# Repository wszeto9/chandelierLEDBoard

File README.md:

# Chandelier LED Board

A bright, addressible LED Panel that is used to light up a chandelier prop. Designed for MIT East Campus REX, Fall 2023.

[Interactive BOM](https://htmlpreview.github.io/?https://raw.githubusercontent.com/wszeto9/chandelierLEDBoard/main/Documentation/ibom.html)

[PDF Schematic](https://github.com/wszeto9/chandelierLEDBoard/blob/7fa08e3c27c50bebdd73984cfcca761c36431bdc/Documentation/schematics.pdf)

<h2> Features:</h2>
<ul>
<li>Single layer stackup for an aluminum PCB to aid in thermal dissipation</li>
<li>8x 9W LEDs, for a total power of approximately 72W.
<li>LEDs are individually addressible, allowing for affects to be shown
<li>Daisy Chainable</li>
<li>Fits on an LGA1155 Cooler for easy cooling
</ul>

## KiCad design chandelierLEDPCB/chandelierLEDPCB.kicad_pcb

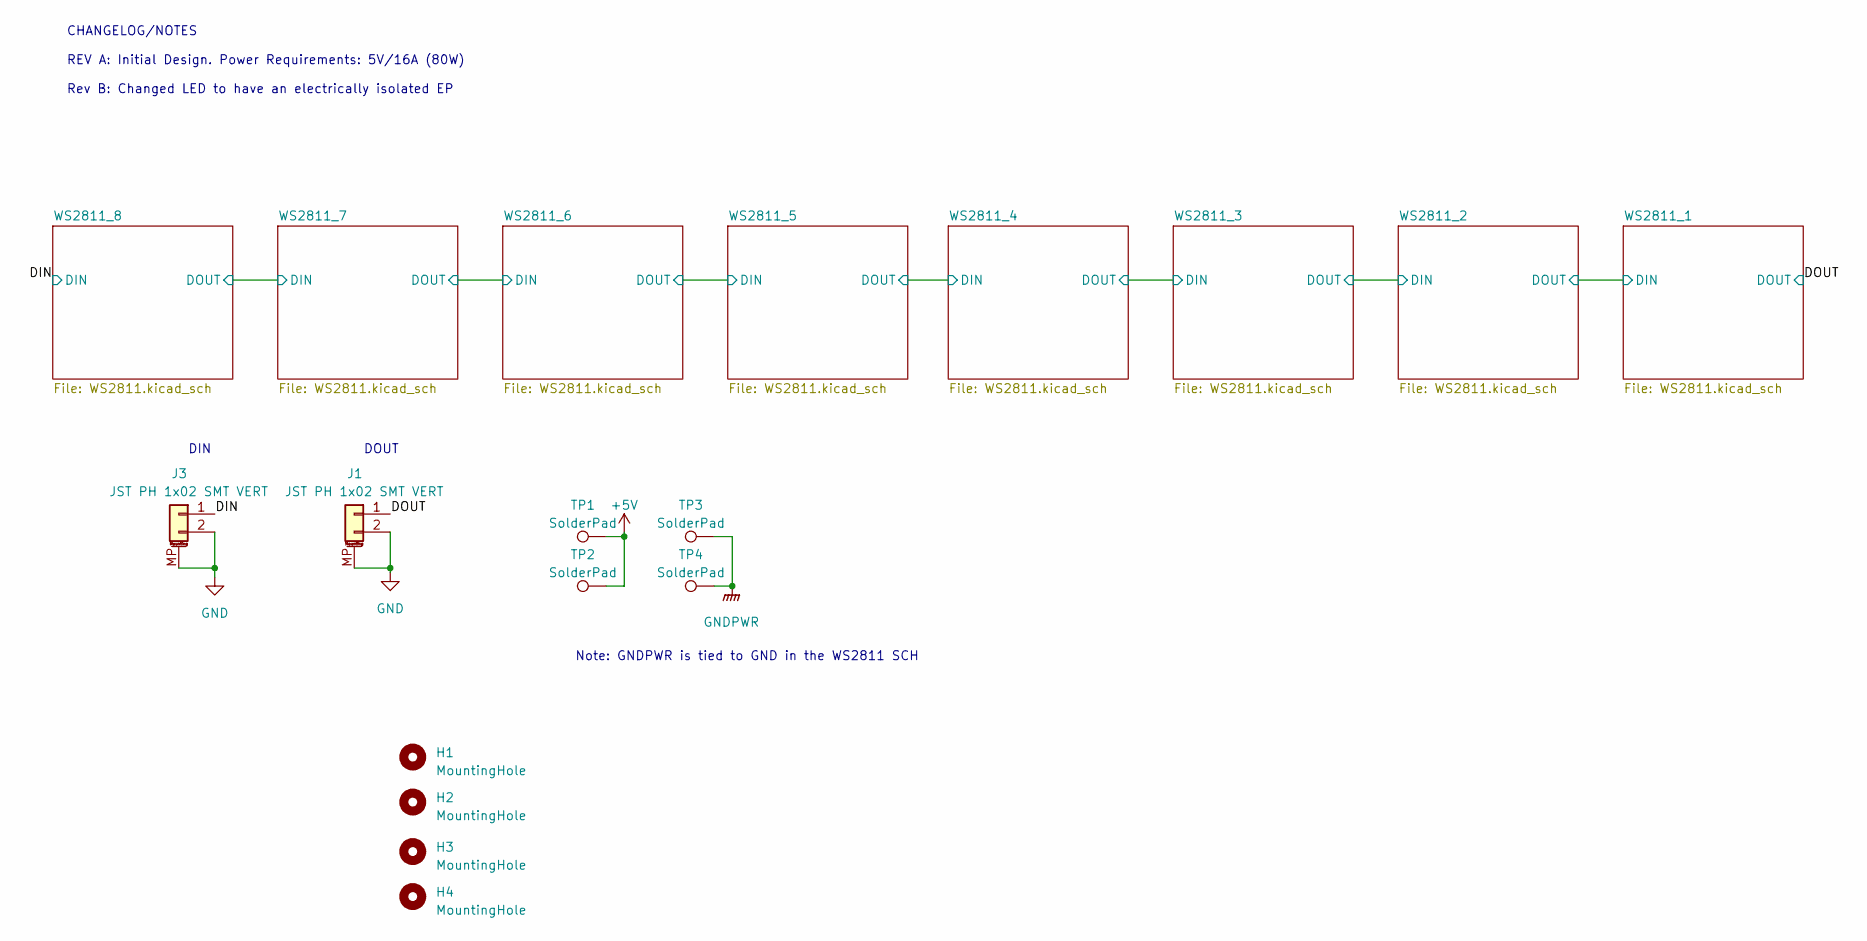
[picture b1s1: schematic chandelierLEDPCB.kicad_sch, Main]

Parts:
H1, H2, H3, H4: MountingHole; MountingHole_3.2mm_M3_DIN965_Pad_TopOnly
J1, J3: JST PH 1x02 SMT VERT; JST_PH_B2B-PH-SM4-TB_1x02-1MP_P2.00mm_Vertical
TP1, TP2, TP3, TP4: SolderPad; TestPoint_Pad_D4.0mm

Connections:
+5V: TP1.1, TP2.1; also elsewhere on the board
/DIN: J3.1; also elsewhere on the board
/DOUT: J1.1; also elsewhere on the board
GND: J1.2, J1.MP (MountPin), J3.2, J3.MP (MountPin); also elsewhere on the board
GNDPWR: TP3.1, TP4.1; also elsewhere on the board

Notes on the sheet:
Note: GNDPWR is tied to GND in the WS2811 SCH
DOUT
DIN
CHANGELOG/NOTES REV A: Initial Design. Power Requirements: 5V/16A (80W) Rev B: Changed LED to have an electrically isolated EP

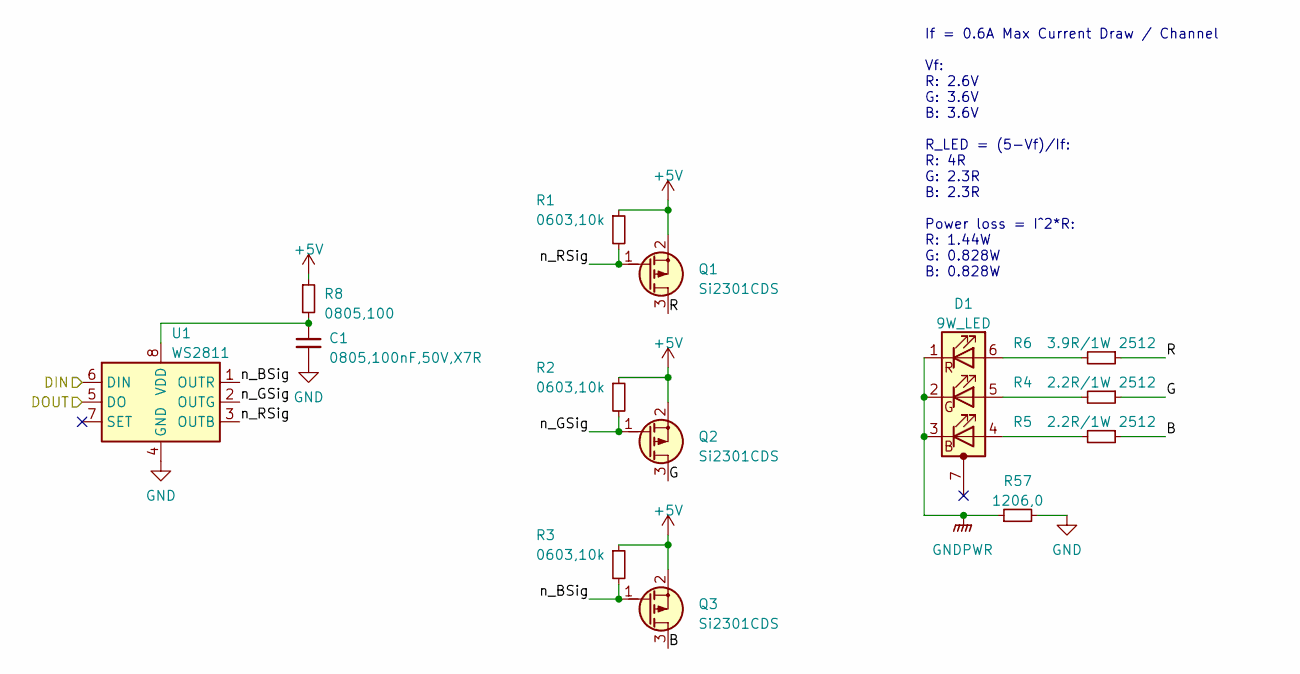
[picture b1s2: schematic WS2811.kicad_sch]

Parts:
C1: 0805,100nF,50V,X7R; C_0805_2012Metric; MFGPN CC0805KRX7R9BB104; LCSC C49678
D1: 9W_LED; 9WLED
Q1, Q2, Q3: Si2301CDS; SOT-23; LCSC C2891731
R1, R2, R3: 0603,10k; R_0603_1608Metric; MFGPN 0603WAF1002T5E; LCSC C25804
R4, R5: 2.2R/1W 2512; R_2512_6332Metric; LCSC C2907574
R6: 3.9R/1W 2512; R_2512_6332Metric; LCSC C2934114
R8: 0805,100; R_0805_2012Metric; MFGPN 0805W8F680JT5E; LCSC C17802
R57: 1206,0; R_1206_3216Metric; MFGPN 1206W4F0000T5E; LCSC C17888
U1: WS2811; SOIC-8_3.9x4.9mm_P1.27mm; LCSC C114581

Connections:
+5V: Q1.2 (S), Q2.2 (S), Q3.2 (S), R1.1, R2.1, R3.1, R8.1; also elsewhere on the board
/DOUT: U1.5 (DO); also elsewhere on the board
/WS2811_1/B: Q3.3 (D), R5.1
/WS2811_1/DIN: U1.6 (DIN); also elsewhere on the board
/WS2811_1/G: Q2.3 (D), R4.1
/WS2811_1/R: Q1.3 (D), R6.1
/WS2811_1/n_BSig: Q3.1 (G), R3.2, U1.1 (OUTR)
/WS2811_1/n_GSig: Q2.1 (G), R2.2, U1.2 (OUTG)
/WS2811_1/n_RSig: Q1.1 (G), R1.2, U1.3 (OUTB)
GND: C1.2, R57.2, U1.4 (GND); also elsewhere on the board
GNDPWR: D1.1 (RK), D1.2 (GK), D1.3 (BK), R57.1; also elsewhere on the board
unnamed: D1.4 (BA), R5.2
unnamed: D1.5 (GA), R4.2
unnamed: D1.6 (RA), R6.2
unnamed: C1.1, R8.2, U1.8 (VDD)

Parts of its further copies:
C2, C3, C4, C5, C6, C7, C8: 0805,100nF,50V,X7R; C_0805_2012Metric; MFGPN CC0805KRX7R9BB104; LCSC C49678
D2, D3, D4, D5, D6, D7, D8: 9W_LED; 9WLED
Q4, Q5, Q6, Q7, Q8, Q9, Q10, Q11, Q12, Q13, Q14, Q15, Q16, Q17, Q18, Q19, Q20, Q21, Q22, Q23, Q24: Si2301CDS; SOT-23; LCSC C2891731
R9, R10, R11, R16, R17, R18, R23, R24, R25, R30, R31, R32, R37, R38, R39, R44, R45, R46, R51, R52, R53: 0603,10k; R_0603_1608Metric; MFGPN 0603WAF1002T5E; LCSC C25804
R12, R19, R26, R33, R40, R47, R54: 3.9R/1W 2512; R_2512_6332Metric; LCSC C2934114
R13, R14, R20, R21, R27, R28, R34, R35, R41, R42, R48, R49, R55, R56: 2.2R/1W 2512; R_2512_6332Metric; LCSC C2907574
R58, R59, R60, R61, R62, R63, R64: 1206,0; R_1206_3216Metric; MFGPN 1206W4F0000T5E; LCSC C17888
U2, U3, U4, U5, U6, U7, U8: WS2811; SOIC-8_3.9x4.9mm_P1.27mm; LCSC C114581

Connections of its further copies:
+5V: Q4.2 (S), Q5.2 (S), Q6.2 (S), Q7.2 (S), Q8.2 (S), Q9.2 (S), Q10.2 (S), Q11.2 (S), Q12.2 (S), Q13.2 (S), Q14.2 (S), Q15.2 (S), Q16.2 (S), Q17.2 (S), Q18.2 (S), Q19.2 (S), Q20.2 (S), Q21.2 (S), Q22.2 (S), Q23.2 (S), Q24.2 (S), R9.1, R10.1, R11.1, R16.1, R17.1, R18.1, R23.1, R24.1, R25.1, R30.1, R31.1, R32.1, R37.1, R38.1, R39.1, R44.1, R45.1, R46.1, R51.1, R52.1, R53.1; also elsewhere on the board
/DIN: U8.6 (DIN); also elsewhere on the board
/WS2811_1/DIN: U2.5 (DO); also elsewhere on the board
/WS2811_2/B: Q6.3 (D), R14.1
/WS2811_2/DIN: U2.6 (DIN), U3.5 (DO)
/WS2811_2/G: Q5.3 (D), R13.1
/WS2811_2/R: Q4.3 (D), R12.1
/WS2811_2/n_BSig: Q6.1 (G), R11.2, U2.1 (OUTR)
/WS2811_2/n_GSig: Q5.1 (G), R10.2, U2.2 (OUTG)
/WS2811_2/n_RSig: Q4.1 (G), R9.2, U2.3 (OUTB)
/WS2811_3/B: Q9.3 (D), R21.1
/WS2811_3/DIN: U3.6 (DIN), U4.5 (DO)
/WS2811_3/G: Q8.3 (D), R20.1
/WS2811_3/R: Q7.3 (D), R19.1
/WS2811_3/n_BSig: Q9.1 (G), R18.2, U3.1 (OUTR)
/WS2811_3/n_GSig: Q8.1 (G), R17.2, U3.2 (OUTG)
/WS2811_3/n_RSig: Q7.1 (G), R16.2, U3.3 (OUTB)
/WS2811_4/B: Q12.3 (D), R28.1
/WS2811_4/DIN: U4.6 (DIN), U5.5 (DO)
/WS2811_4/G: Q11.3 (D), R27.1
/WS2811_4/R: Q10.3 (D), R26.1
/WS2811_4/n_BSig: Q12.1 (G), R25.2, U4.1 (OUTR)
/WS2811_4/n_GSig: Q11.1 (G), R24.2, U4.2 (OUTG)
/WS2811_4/n_RSig: Q10.1 (G), R23.2, U4.3 (OUTB)
/WS2811_5/B: Q15.3 (D), R35.1
/WS2811_5/DIN: U5.6 (DIN), U6.5 (DO)
/WS2811_5/G: Q14.3 (D), R34.1
/WS2811_5/R: Q13.3 (D), R33.1
/WS2811_5/n_BSig: Q15.1 (G), R32.2, U5.1 (OUTR)
/WS2811_5/n_GSig: Q14.1 (G), R31.2, U5.2 (OUTG)
/WS2811_5/n_RSig: Q13.1 (G), R30.2, U5.3 (OUTB)
/WS2811_6/B: Q18.3 (D), R42.1
/WS2811_6/DIN: U6.6 (DIN), U7.5 (DO)
/WS2811_6/G: Q17.3 (D), R41.1
/WS2811_6/R: Q16.3 (D), R40.1
/WS2811_6/n_BSig: Q18.1 (G), R39.2, U6.1 (OUTR)
/WS2811_6/n_GSig: Q17.1 (G), R38.2, U6.2 (OUTG)
/WS2811_6/n_RSig: Q16.1 (G), R37.2, U6.3 (OUTB)
/WS2811_7/B: Q21.3 (D), R49.1
/WS2811_7/DIN: U7.6 (DIN), U8.5 (DO)
/WS2811_7/G: Q20.3 (D), R48.1
/WS2811_7/R: Q19.3 (D), R47.1
/WS2811_7/n_BSig: Q21.1 (G), R46.2, U7.1 (OUTR)
/WS2811_7/n_GSig: Q20.1 (G), R45.2, U7.2 (OUTG)
/WS2811_7/n_RSig: Q19.1 (G), R44.2, U7.3 (OUTB)
/WS2811_8/B: Q24.3 (D), R56.1
/WS2811_8/G: Q23.3 (D), R55.1
/WS2811_8/R: Q22.3 (D), R54.1
/WS2811_8/n_BSig: Q24.1 (G), R53.2, U8.1 (OUTR)
/WS2811_8/n_GSig: Q23.1 (G), R52.2, U8.2 (OUTG)
/WS2811_8/n_RSig: Q22.1 (G), R51.2, U8.3 (OUTB)
GND: C2.2, C3.2, C4.2, C5.2, C6.2, C7.2, C8.2, R58.2, R59.2, R60.2, R61.2, R62.2, R63.2, R64.2, U2.4 (GND), U3.4 (GND), U4.4 (GND), U5.4 (GND), U6.4 (GND), U7.4 (GND), U8.4 (GND); also elsewhere on the board
GNDPWR: D2.1 (RK), D2.2 (GK), D2.3 (BK), D3.1 (RK), D3.2 (GK), D3.3 (BK), D4.1 (RK), D4.2 (GK), D4.3 (BK), D5.1 (RK), D5.2 (GK), D5.3 (BK), D6.1 (RK), D6.2 (GK), D6.3 (BK), D7.1 (RK), D7.2 (GK), D7.3 (BK), D8.1 (RK), D8.2 (GK), D8.3 (BK), R58.1, R59.1, R60.1, R61.1, R62.1, R63.1, R64.1; also elsewhere on the board
unnamed: D2.4 (BA), R14.2
unnamed: D2.5 (GA), R13.2
unnamed: D2.6 (RA), R12.2
unnamed: D3.4 (BA), R21.2
unnamed: D3.5 (GA), R20.2
unnamed: D3.6 (RA), R19.2
unnamed: D4.4 (BA), R28.2
unnamed: D4.5 (GA), R27.2
unnamed: D4.6 (RA), R26.2
unnamed: D5.4 (BA), R35.2
unnamed: D5.5 (GA), R34.2
unnamed: D5.6 (RA), R33.2
unnamed: D6.4 (BA), R42.2
unnamed: D6.5 (GA), R41.2
unnamed: D6.6 (RA), R40.2
unnamed: D7.4 (BA), R49.2
unnamed: D7.5 (GA), R48.2
unnamed: D7.6 (RA), R47.2
unnamed: D8.4 (BA), R56.2
unnamed: D8.5 (GA), R55.2
unnamed: D8.6 (RA), R54.2
unnamed 85: C2.1, U2.8 (VDD); also elsewhere on the board
unnamed 86: C3.1, U3.8 (VDD); also elsewhere on the board
unnamed 87: C4.1, U4.8 (VDD); also elsewhere on the board
unnamed 88: C5.1, U5.8 (VDD); also elsewhere on the board
unnamed 89: C6.1, U6.8 (VDD); also elsewhere on the board
unnamed 90: C7.1, U7.8 (VDD); also elsewhere on the board
unnamed 91: C8.1, U8.8 (VDD); also elsewhere on the board

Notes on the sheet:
If = 0.6A Max Current Draw / Channel Vf: R: 2.6V G: 3.6V B: 3.6V R_LED = (5-Vf)/If: R: 4R G: 2.3R B: 2.3R Power loss = I^2*R: R: 1.44W G: 0.828W B: 0.828W

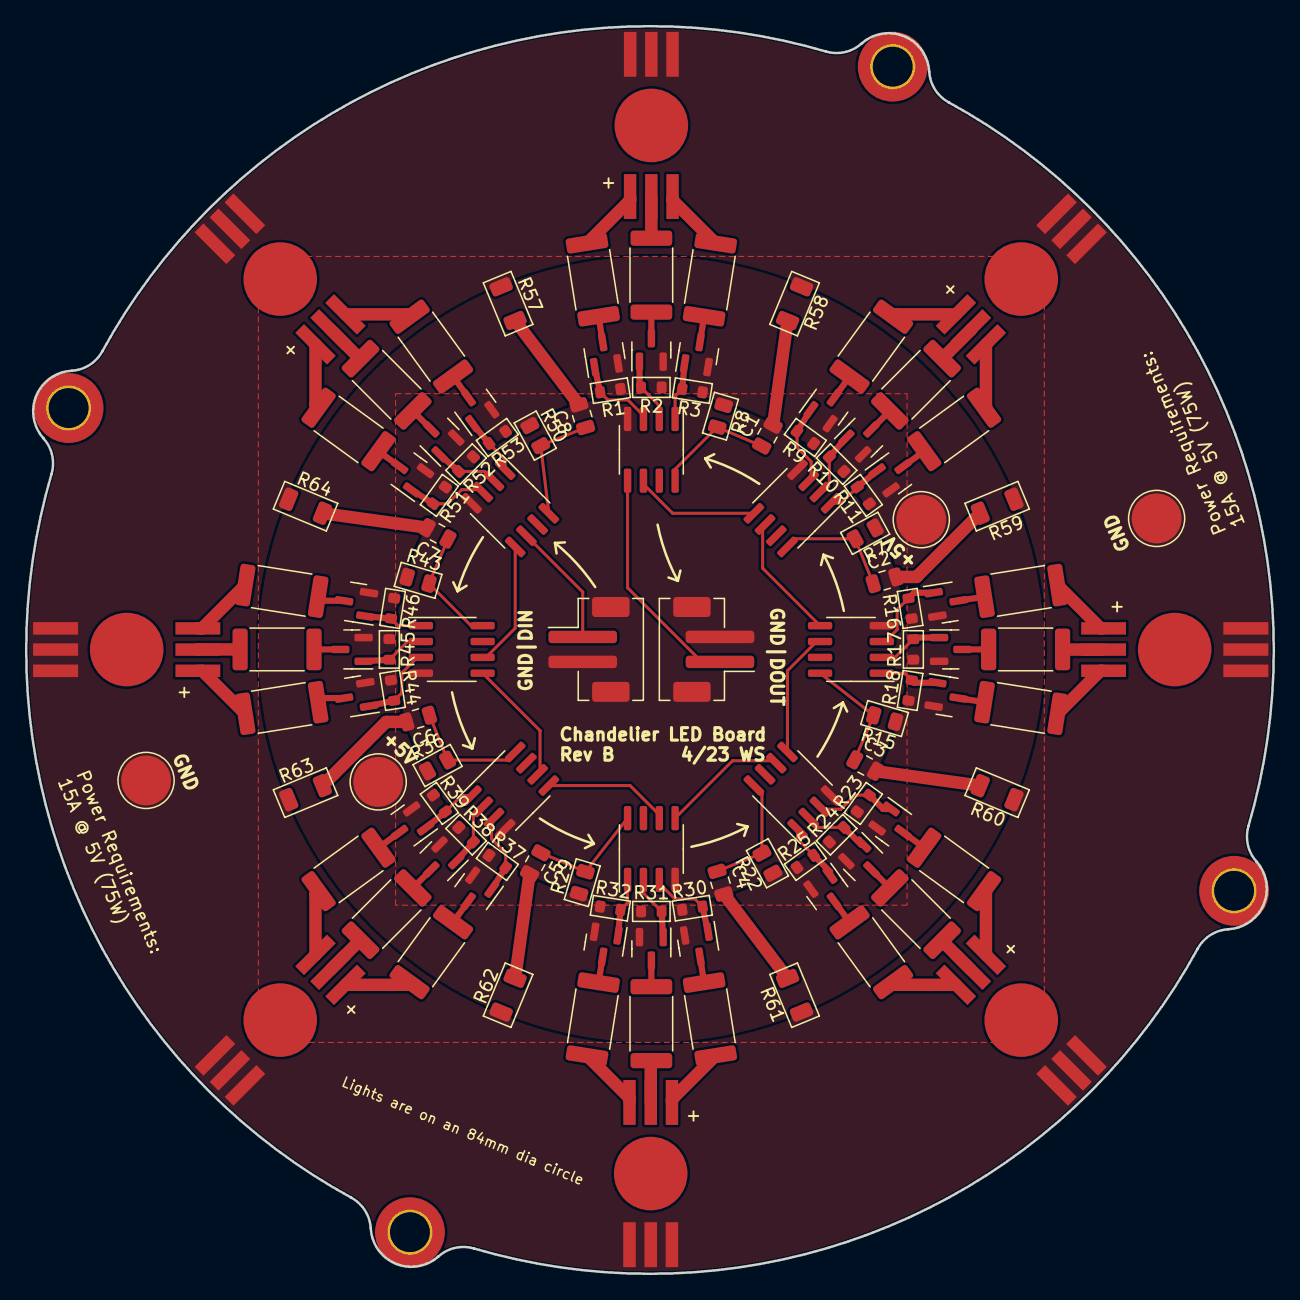
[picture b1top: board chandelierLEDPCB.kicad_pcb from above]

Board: 2 copper layers, 100.0 x 100.0 mm, 122 parts (0 on the bottom side), 92 nets.

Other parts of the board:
R7, R15, R22, R29, R36, R43, R50: 0805,68; R_0805_2012Metric

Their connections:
+5V: R7.1, R15.1, R22.1, R29.1, R36.1, R43.1, R50.1; also elsewhere on the board
unnamed 85: R7.2; also elsewhere on the board
unnamed 86: R15.2; also elsewhere on the board
unnamed 87: R22.2; also elsewhere on the board
unnamed 88: R29.2; also elsewhere on the board
unnamed 89: R36.2; also elsewhere on the board
unnamed 90: R43.2; also elsewhere on the board
unnamed 91: R50.2; also elsewhere on the board

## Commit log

2023-04-02 Routed traces
2023-04-08 Changed board outline
2023-04-08 updated schematic to include rev, edited sheet size
2023-04-24 Added edge cuts and paste SVG for laser cutting stencil
2023-04-24 Edited LED to have EP disconnected
2024-01-28 cleaned up
